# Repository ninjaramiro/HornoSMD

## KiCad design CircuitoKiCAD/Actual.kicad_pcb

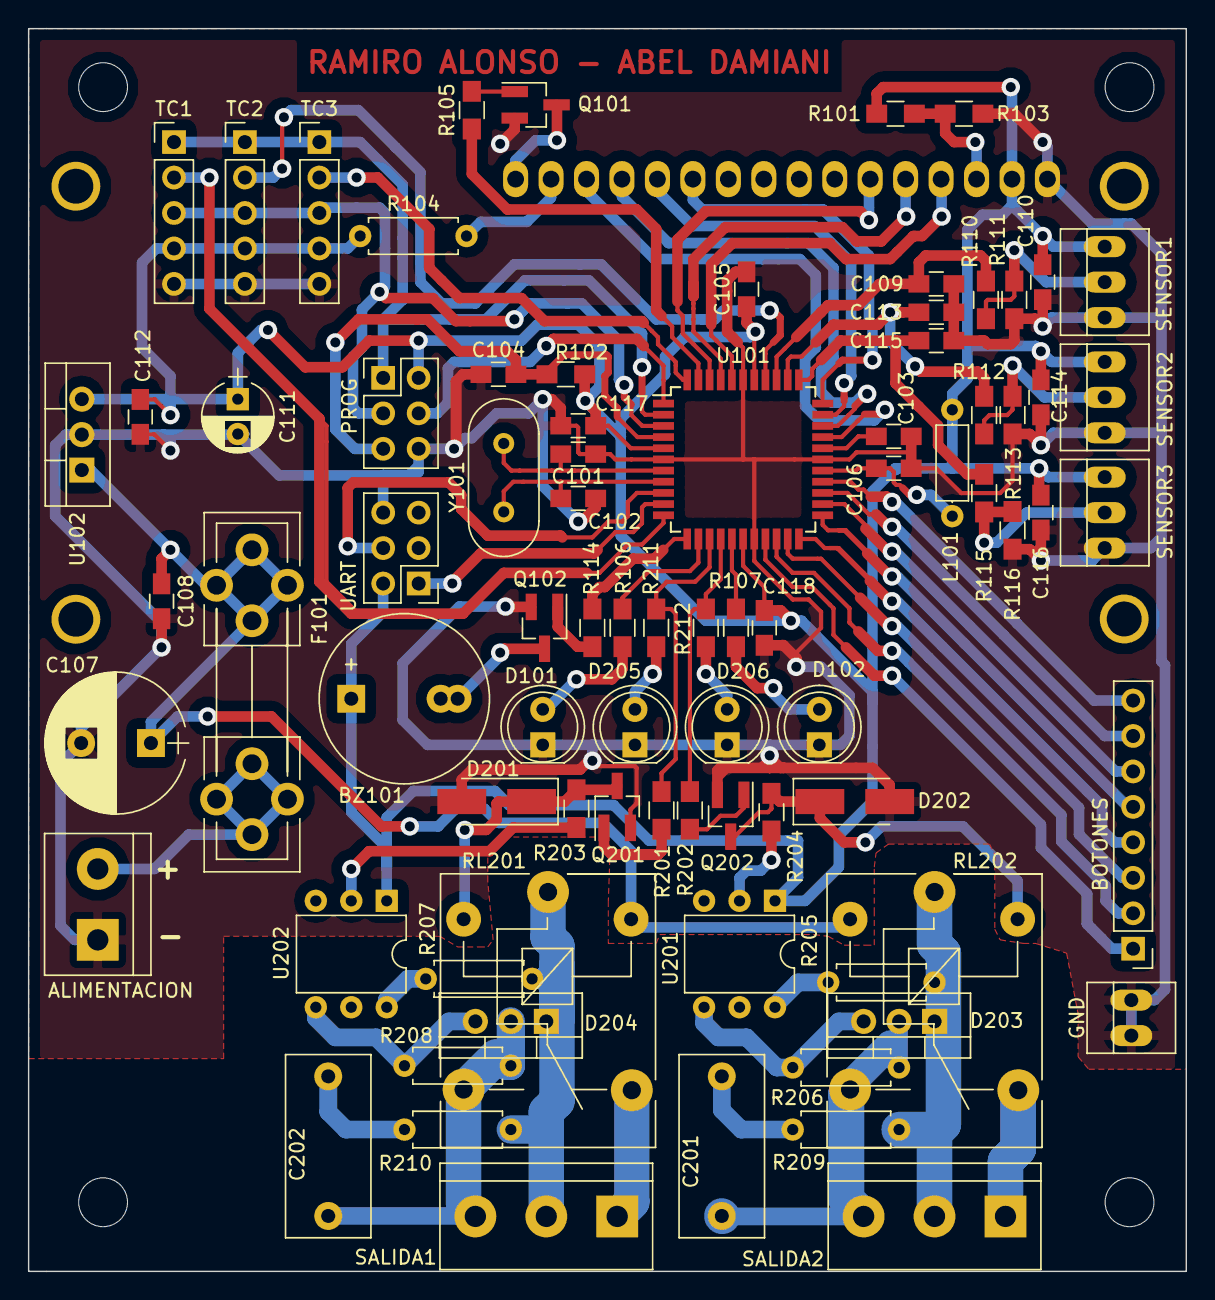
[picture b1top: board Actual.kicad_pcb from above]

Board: 2 copper layers, 82.9 x 89.0 mm, 86 parts (1 on the bottom side), 72 nets.

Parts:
ALIMENTACION: FUENTE12V; bornier2
BOTONES: Aux; Pin_Header_Straight_1x08_Pitch2.54mm
BZ101: Buzzer
C101, C102: 22p; C_0805_HandSoldering
C103, C104, C105, C106, C108, C109, C110, C112, C113, C114, C115, C116, C117, C118: 100n; C_0805_HandSoldering
C107: 1000u x16v; CP_Radial_D10.0mm_P5.00mm
C111: 100u; CP_Radial_D5.0mm_P2.50mm
C201, C202: 0.01u 630v; C_Rect_L13.0mm_W6.0mm_P10.00mm_FKS3_FKP3_MKS4
D101, D102, D205, D206: LED; LED_D5.0mm
D201, D202: 1n4007; D_SMA_Handsoldering
D203, D204: BTA24; TO-220_Vertical
DS101: LCD16X2; 1602B
F101: Fuse; Fuseholder5x20_horiz_open_universal_Type-III
GND: GND; PINHEAD1-2
L101: L; L_Axial_L5.3mm_D2.2mm_P7.62mm_Horizontal_Vishay_IM-1
MK101, MK102, MK103, MK104: Mounting_Hole; MountingHole_3.5mm
PROG: PROG; Pin_Header_Straight_2x03_Pitch2.54mm
Q101, Q102, Q201, Q202: BC817; SOT-23_Handsoldering
R101, R102, R114, R201, R202: 10k; R_0805_HandSoldering
R103, R105, R110, R112, R115: 1k; R_0805_HandSoldering
R104: 100; R_Axial_DIN0207_L6.3mm_D2.5mm_P7.62mm_Horizontal
R106, R107, R211, R212: 470; R_0805_HandSoldering
R111, R113, R116, R203, R204: TBD; R_0805_HandSoldering
R205, R207: 360; R_Axial_DIN0207_L6.3mm_D2.5mm_P7.62mm_Horizontal
R206, R208: 330; R_Axial_DIN0207_L6.3mm_D2.5mm_P7.62mm_Horizontal
R209, R210: 39R; R_Axial_DIN0207_L6.3mm_D2.5mm_P7.62mm_Horizontal
RL201, RL202: RELAY; Relay_SANYOU_SRD_Series_Form_C
SALIDA1, SALIDA2: SALIDA2; bornier3
SENSOR1, SENSOR2, SENSOR3: LM35; PINHEAD1-3
TC1, TC2, TC3: CONN_01X05; Pin_Header_Straight_1x05_Pitch2.54mm
U101: ATMEGA16A-AU; TQFP-44_10x10mm_Pitch0.8mm
U102: LM7805CT; TO-220_Vertical
U201, U202: MOC3063M; DIP-6_W7.62mm
UART: PROG; Pin_Header_Straight_2x03_Pitch2.54mm
Y101: Crystal; Crystal_HC18-U_Vertical

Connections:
+5V: BZ101.1, C105.1, C110.1, C111.1, C112.1, C114.1, C116.1, C117.1, C118.1, DS101.2, L101.1, PROG.2, R101.2, R102.1, R104.1, SENSOR1.3, SENSOR2.3, SENSOR3.3, TC1.4, TC2.4, TC3.4, U101.5, U101.17, U101.38, U102.3, U201.1, U202.1, UART.2
/BacklightLCD: R105.2, U101.43
/Buzzer: R114.1, U101.12
/CS_1: TC1.2, U101.11
/CS_2: TC2.2, U101.37
/CS_3: TC3.2, U101.44
/LCD_D4: DS101.11, U101.33
/LCD_D5: DS101.12, U101.32
/LCD_D6: DS101.13, U101.31
/LCD_D7: DS101.14, U101.30
/LCD_E: DS101.6, U101.42
/LCD_RS: DS101.4, U101.40
/LCD_RW: DS101.5, U101.41
/Led_1: R106.2, U101.13
/Led_2: R107.2, U101.16
/MISO: PROG.1, TC1.1, TC2.1, TC3.1, U101.2
/MOSI: PROG.4, U101.1
/RST: C104.2, PROG.5, R102.2, U101.4
/RXD_AVR: U101.9, UART.4
/SCK: PROG.3, TC1.3, TC2.3, TC3.3, U101.3
/Salida1: R201.2, R211.2, U101.14
/Salida2: R202.2, R212.2, U101.15
/TXD_AVR: U101.10, UART.1
/Temp1: C109.1, R110.2, U101.36
/Temp2: C113.1, R112.2, U101.35
/Temp3: C115.1, R115.2, U101.34
/aux1: BOTONES.1, U101.19
/aux2: BOTONES.2, U101.20
/aux3: BOTONES.3, U101.21
/aux4: BOTONES.4, U101.22
/aux5: BOTONES.5, U101.23
/aux6: BOTONES.6, U101.24
/aux7: BOTONES.7, U101.25
/aux8: BOTONES.8, U101.26
GND: ALIMENTACION.1, C101.2, C102.2, C103.2, C104.1, C105.2, C106.2, C107.2, C108.2, C109.2, C110.2, C111.2, C112.2, C113.2, C114.2, C115.2, C116.2, C117.2, C118.2, D101.1, D102.1, D201.2, D202.2, D205.1, D206.1, DS101.1, GND.1, GND.2, PROG.6, Q101.2, Q102.2, Q201.2, Q202.2, R103.1, R111.1, R113.1, R116.1, SENSOR1.1, SENSOR2.1, SENSOR3.1, TC1.5, TC2.5, TC3.5, U101.6, U101.18, U101.28, U101.39, U102.2, UART.6
unnamed: BZ101.2, Q102.3
unnamed: C101.1, U101.7, Y101.1
unnamed: C102.1, U101.8, Y101.2
unnamed: C103.1, U101.29
unnamed: C106.1, L101.2, U101.27
unnamed: C201.1, R209.1
unnamed: C201.2, D203.2, R206.1, RL202.3, SALIDA2.3
unnamed: C202.1, R210.1
unnamed: C202.2, D204.2, R208.1, RL201.3, SALIDA1.3
unnamed: D101.2, R106.1
unnamed: D102.2, R107.1
unnamed: D201.1, Q201.3, R203.2, RL201.2
unnamed: D202.1, Q202.3, R204.2, RL202.5
unnamed: D203.1, R205.1, R209.2, RL202.1, SALIDA2.2
unnamed: D203.3, R206.2, U201.4
unnamed: D204.1, R207.1, R210.2, RL201.1, SALIDA1.2
unnamed: D204.3, R208.2, U202.4
unnamed: D205.2, R211.1
unnamed: D206.2, R212.1
unnamed: DS101.3, R101.1, R103.2
unnamed: DS101.15, R104.2
unnamed: DS101.16, Q101.3
unnamed: ALIMENTACION.2, F101.2
unnamed: R110.1, R111.2, SENSOR1.2
unnamed: R112.1, R113.2, SENSOR2.2
unnamed: R115.1, R116.2, SENSOR3.2
unnamed: RL202.4, SALIDA2.1
unnamed: RL201.4, SALIDA1.1
unnamed: Q101.1, R105.1
unnamed: Q102.1, R114.2
unnamed: Q201.1, R201.1
unnamed: Q202.1, R202.1
unnamed: R203.1, U202.2
unnamed: R204.1, U201.2
unnamed: R205.2, U201.6
unnamed: R207.2, U202.6
VDD: C107.1, C108.1, F101.1, RL201.5, RL202.2, U102.1

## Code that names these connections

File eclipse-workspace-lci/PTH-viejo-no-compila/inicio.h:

/*
 * FUENTE PTH - CONFIGURACION DE LOS PUERTOS
 * PIN 1 → RESET
 * PIN 2 → RXD - PTO SERIE
 * PIN 3 → TXD - PTO SERIE
 * PIN 4 → PD2 - LCD_RS
 * PIN 5 → PD3 - LCD_RW
 * PIN 6  → PD4 - LCD_E
 * PIN 11 → PD5 - LCD_D4
 * PIN 12 → PD6 - LCD_D5
 * PIN 13 → PD7 - LCD_D6
 * PIN 14 → PB0 - LCD_D7
 * PIN 15 → PB1 - PWM1
 * PIN 16 → PB2 - PWM2
 *
 * PIN 17 → PB3 - MOSI - BOT_4
 * PIN 18 → PB4 - MISO - BOT_3
 * PIN 19 → PB5 - SCK - BOT_2
 *
 * PIN 23 → PC0 - BOT_1
 * PIN 24 → PC1 - POTE
 * PIN 25 → PC2 - BUZZER
 * PIN 26 → PC3 - PULSE_2
 * PIN 27 → PC4 - SENS_CORRIENTE
 * PIN 28 → PC5 - PULSE_1
 *
 */

#ifndef INICIO_H_
#define INICIO_H_

//#define __AVR_ATmega328P__
#include <avr/io.h>



/*****************************************************************************
* Prototipos
*****************************************************************************/

void Inicio_Puertos (void);

void Inicio_Timer0 (void);

//void Inicio_Timer1 (void);

void Inicio_Timer2 (void);

void Inicio_PWM (void);



/*****************************************************************************
* Definicion de los nombres de los puertos
*****************************************************************************/

#define USART_PORT				PORTD
#define USART_DDR     		DDRD
#define USART_RXD					PD0
#define USART_TXD					PD1

#define BOT_1					  PC0
#define BOT_1_PORT			PORTC
#define BOT_1_PIN				PINC
#define BOT_1_DDR	      DDRC

#define BOT_2					  PB5
#define BOT_2_PORT			PORTB
#define BOT_2_PIN				PINB
#define BOT_2_DDR	      DDRB

#define BOT_3					  PB4
#define BOT_3_PORT			PORTB
#define BOT_3_PIN				PINB
#define BOT_3_DDR       DDRB

#define BOT_4					  PB3
#define BOT_4_PORT			PORTB
#define BOT_4_PIN				PINB
#define BOT_4_DDR	      DDRB

#define POTE						PC1
#define POTE_PORT				PORTC
#define POTE_PIN				PINC
#define POTE_DDR    		DDRC

#define BUZZER						PC2
#define BUZZER_PORT				PORTC
#define BUZZER_PIN				PINC
#define BUZZER_DDR    		DDRC

#define PULSE2						PC3
#define PULSE2_PORT				PORTC
#define PULSE2_PIN				PINC
#define PULSE2_DDR		DDRC

#define SENS_CORRIENTE						PC4
#define SENS_CORRIENTE_PORT				PORTC
#define SENS_CORRIENTE_PIN				PINC
#define SENS_CORRIENTE_DDR    		DDRC

#define PULSE1						PC5
#define PULSE1_PORT				PORTC
#define PULSE1_PIN				PINC
#define PULSE1_DDR		DDRC

#define PWM1						PB1
#define PWM1_PORT				PORTB
#define PWM1_PIN				PINB
#define PWM1_DDR    		DDRB

#define PWM2						PB2
#define PWM2_PORT				PORTB
#define PWM2_PIN				PINB
#define PWM2_DDR		    DDRB

#define LCD_RS						PD2
#define LCD_RS_PORT			  PORTD
#define LCD_RS_PIN				PIND
#define LCD_RS_DDR    	  DDRD

#define LCD_RW						PD3
#define LCD_RW_PORT			  PORTD
#define LCD_RW_PIN				PIND
#define LCD_RW_DDR    	  DDRD

#define LCD_E						PD4
#define LCD_E_PORT			PORTD
#define LCD_E_PIN				PIND
#define LCD_E_DDR     	DDRD

#define LCD_D4						PD5
#define LCD_D4_PORT			  PORTD
#define LCD_D4_PIN				PIND
#define LCD_D4_DDR	      DDRD

#define LCD_D5						PD6
#define LCD_D5_PORT			  PORTD
#define LCD_D5_PIN				PIND
#define LCD_D5_DDR	      DDRD

#define LCD_D6						PD7
#define LCD_D6_PORT			  PORTD
#define LCD_D6_PIN				PIND
#define LCD_D6_DDR    	  DDRD

#define LCD_D7						PB0
#define LCD_D7_PORT			  PORTB
#define LCD_D7_PIN				PINB
#define LCD_D7_DDR	      DDRB



#endif /* INICIO_H_ */

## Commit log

2020-03-18 Inicio del GIT. Agregué todos los archivos que tenía sobre el proyecto.
2020-03-18 Agrego un firmware dentro de la carpeta firmwares viejos con código para manejar el integrado de la termocupla.
2020-03-27 Agregué un ejemplo con la estructura deseada del código.
2020-05-22 Commit inicial de TERMOSTATO
2020-05-22 Prueba de leds. Titilan los 4 leds
2020-05-22 mejoras menores
